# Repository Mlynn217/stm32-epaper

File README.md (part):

# stm32-epaper

An STM32-based e-reader using the Waveshare 6inch HD e-Paper HAT (IT8951 controller).

## Current Status

**Reads a real EPUB off an SD card and renders actual book pages on the physical panel.** On real
hardware, confirmed working end to end:
- STM32CubeMX → CMake → arm-none-eabi-gcc/Ninja → OpenOCD → ST-LINK build/flash/debug loop, from
  inside VSCode (tasks + launch configs for build, flash, debug, and a serial monitor)
- SPI1 communication with the IT8951 (panel resolution/FW/LUT version read back correctly, this
  panel's VCOM `-2.59V` set), the FMC/SDRAM (16MB, full read/write test passes), full-panel GC16
  grayscale refresh, and A2 (fast black/white-only partial refresh) mode
- **SD card storage** — SDIO+FatFS mount/read/write, a directory listing on every boot, and long
  filename support (`_USE_LFN=3`, heap-based — see TODO.md for why not `1`/`2`)
- **Fonts and page layout** — anti-aliased proportional bitmap fonts at reading-appropriate sizes
  (generated from a real TTF via `tools/gen_font.py`, not the tiny fixed-width fonts a low-res TFT
  would use), word-wrap, and pagination (a continuation-pointer API that can paginate arbitrarily
  long text one screen at a time without holding more than one page in memory)
- **An EPUB reader** (`Drivers/Epub/`, `Drivers/Inflate/`) — a minimal ZIP reader, a vendored
  reference DEFLATE decompressor, and tiny XML/HTML helpers, enough to parse `container.xml` → the
  OPF's manifest/spine → a chapter's XHTML → clean plain text, fed straight into the page-layout
  pipeline above. Validated against a real book (a purchased copy of *Mistborn: Secret History*) —
  see TODO.md for the debugging story, including a real FatFs/SDIO stale-read bug found and worked
  around along the way

Not done yet — see [TODO.md](TODO.md) for the full list, but the near-term highlights:
- No page-turn/chapter-navigation UI yet (currently auto-picks the first chapter with real text and
  shows up to 4 pages of it); no physical input handling
- Power management/battery life not started
- Custom PCB: the **v1 schematic is drafted in full** in `hardware/kicad/` (Power, MCU, Memory and
  Peripherals sheets). It's ERC-clean and machine-checked (pin mux, nets, footprint pads), but not
  yet reviewed by a person. v1 scope: the Waveshare HAT stays external on an SPI connector (see
  [Custom PCB (Planned)](#custom-pcb-planned))
- Custom PCB layout **nearly routed**: `hardware/kicad/stm32-epaper.kicad_pcb` is placed and
  routed (4 layers, enclosure-derived outline, inner planes) except **2 of ~460 connections**,
  both at the CAP1188. Some SDRAM/SDIO length and skew rules still need tuning (see TODO.md and
  [Layout rules](#layout-rules-main-board)). It's scripted end to end: placement,
  pre-routing, offline freerouting and our own last-mile router, with every attempt in
  `hardware/kicad/routing-log.md`. The side-wall electrode board (`hardware/electrode/`) is
  fully laid out and DRC-clean
- Enclosure: a **v0 parametric draft** in `hardware/enclosure/` (build123d). It passes its own fit
  checks and exports STEP/STL/3MF, but several dimensions are still placeholders and nothing has
  been printed (see [Enclosure](#enclosure-v0-draft))
- No license chosen yet

## Overview

Goal: a standalone, **handheld, Kindle-style** e-reader built around Waveshare's
[6inch HD e-Paper HAT](https://www.waveshare.com/6inch-hd-e-paper-hat.htm) (1448×1072, 16-level
grayscale, IT8951 controller), driven by an STM32 host. The Discovery board is a bring-up platform;
the end goal is a custom PCB — see [Custom PCB (Planned)](#custom-pcb-planned) below for the current
draft of hardware decisions for that board.

**Phase 1 host: STM32F469I-DISCO.** It has its own onboard RGB LCD, but that's not why it was
picked — it's the FMC-attached SDRAM that matters. The IT8951 needs a host-side frame buffer too
large for any STM32's internal SRAM, which is exactly why Waveshare's own reference design pairs
the IT8951 with an STM32F429 board (Open429I) that has external SDRAM bolted on. The F469-Disco
already has SDRAM on the FMC bus (normally used for its own LCD), so we get that requirement for
free. It's a bring-up/development platform for proving out the driver and architecture — the final
product host may end up being a smaller, lower-power part once the design is proven.

## Hardware

### Display: Waveshare 6inch HD e-Paper HAT

- Panel: 6", 1448×1072, black/white, 16 grayscale levels (1–4 bpp)
- Controller: IT8951 (on the HAT/driver board)
- Full refresh: <1s. Refresh power ~0.6W typ, standby ~0.3W typ
- Host interface options: SPI / I80 (parallel) / I2C / USB (USB requires an NDA with Waveshare —
  not an option for us)
- **Using SPI** — Waveshare's own recommendation ("fewer pins, easy to use"). I80 is faster but
  needs 16 data pins plus control lines, which would compete with the Discovery board's other
  onboard peripherals; I2C is too slow for meaningful refresh rates.
- Operating voltage: 5V
- Outline: 138.4×101.8×0.67mm; active display area: 122.356×90.584mm
- Viewing angle: >170°; operating temp 0–50°C, storage -25–70°C
- Each physical panel has a unique **VCOM** value printed on its FPC cable that must be set in
  firmware for correct grayscale/contrast. **This panel's VCOM is `-2.59V`** → pass `2590` (mV
  magnitude) to `EPD_IT8951_Init()`/`EPD_IT8951_SetVCOM()`.

### Host: STM32F469I-DISCO

- STM32F469NIH6 — Cortex-M4F, 2MB flash, 384KB internal SRAM
- FMC-attached SDRAM onboard (normally the framebuffer for the board's own RGB LCD) — repurposed
  here as the IT8951 frame buffer
- Onboard ST-LINK/V2-1 — no external debug probe needed

### Wiring

Final pin assignment for the F469-Disco, chosen by checking every candidate pin against the MCU's
full alternate-function list and cross-referencing everything already enabled in the `.ioc` (FMC,
DSIHOST/LTDC, I2C1/2, SAI1, SDIO, QUADSPI, USART3/6, USB_OTG_FS, TIM1) — no conflicts:

| IT8951 HAT pin | Signal              | STM32 pin | Discovery connector      | Pin # | Silkscreen label | Wire color |
|----------------|---------------------|-----------|--------------------------|-------|-------------------|------------|
| 5V             | Power               | —         | CN6 (Arduino Power)      | 5     | `+5V`             | Grey       |
| GND            | Ground              | —         | CN6 (Arduino Power)      | 6/7   | `GND`             | Black      |
| SCK            | SPI1_SCK            | PA5       | CN12 (Extension header)  | 7     | —                 | Orange     |
| MISO           | SPI1_MISO           | PB4       | CN12 (Extension header)  | 5     | —                 | Blue       |
| MOSI           | SPI1_MOSI           | PB5       | CN12 (Extension header)  | 9     | —                 | Yellow     |
| CS             | GPIO_Output, PP, idle high | PA4 | CN8 (Arduino Analog)   | 6     | `A5`              | Green      |
| RST            | GPIO_Output, PP, idle high | PB1 | CN8 (Arduino Analog)   | 1     | `A0`              | White      |
| HRDY (busy)    | GPIO_Input          | PA2       | CN7 (Arduino Digital)    | 6     | `D5`              | Purple     |

Notes:
- SPI1's SCK/MISO/MOSI are only broken out on **CN12**, the 16-pin 2.54mm extension header on the
  underside of the board — not on the Arduino headers. CS/RST/HRDY are split across CN8 and CN7
  instead, so wiring the HAT means jumpers from three different connectors plus CN6, not one.
- CN8 pin 6 (`A5`) defaults to PA4 via solder bridges SB10/SB12 (closed by default) — worth a
  continuity check with a multimeter before trusting it, since those can be reconfigured.
- CS/RST are push-pull, idle **high** (both signals are active-low on the IT8951 side — CS is only
  pulled low during a transaction, RST is only pulsed low as a deliberate reset, driven by the
  driver's init code rather than left low by default).
- SPI1 clock: **11.25 MHz** (APB2/8 off a 90MHz APB2 clock). The IT8951's datasheet (Table 9-4, SPI
  AC Characteristics) caps `fSCLK` at 24MHz; 11.25MHz leaves comfortable margin for jumper-wire
  wiring rather than a tightly-routed PCB. `hspi1.Init.BaudRatePrescaler` in `Core/Src/main.c` and
  `SPI1.CalculateBaudRate` in the `.ioc` are both set to match.
- HRDY (busy) is active-low (low = busy). All three IT8951-side GPIOs are currently `GPIO_NOPULL`
  (no pull-up/down) — a defensive pull-up was considered for the brief post-reset window before
  `MX_GPIO_Init()` runs, but wasn't applied; not required since these are actively driven once init
  runs, just an optional safety margin if boot-order issues ever show up.

## Custom PCB (Planned)

In progress. The KiCad project is in `hardware/kicad/`, and the **v1 schematic is drafted in full**:
Power, MCU, Memory and Peripherals sheets. PCB layout is next (see TODO.md). These are the
**current draft hardware decisions**, recorded here so context isn't lost between sessions. They're still open to change
while the schematic takes shape. The Discovery board plus the Waveshare HAT above stays the bring-up
platform until the PCB is built.

**Board scope (decided 2026-09-22):**
- **v1 PCB:** power, MCU, memory, navigation/input and the other peripherals. The **Waveshare
  IT8951 HAT stays an external module**, connected over an SPI connector, with the board supplying
  its 5 V.
- **Deferred to a later revision:** a bare IT8951 IC with its own panel PMIC (see
  [Display](#display) for what that involves).

### Input System

| Control | Component | Interface | Notes |
|---|---|---|---|
| Prev / Next page | CAP1188-1-SL (Microchip) | I²C + ALERT interrupt | 8-channel; side-wall electrodes |
| Side-wall electrodes | 2 small electrode boards (0.8 mm FR4), 2 pads each | JST-SH cable per side (J302/J303) | Pads pressed against the inside of each side wall; plastic wall as dielectric (up to ~4mm) |
| Library / menu scroll | Bourns PEC11R-4220F-S0024 | 2× GPIO (A, B quadrature) | 24 detents / 24 pulses per revolution, 20mm flatted shaft (the M7 bushing leaves too little of a 15mm shaft for the knob to grip through the front face; the Discovery bring-up used the 15mm -4215F) |
| Confirm / select | Encoder push | 1× GPIO (SW) | Built into the PEC11R (the "S" in S0024) |
| Power / wake | Alps SKRTLAE010 side-actuated tact switch | 1× GPIO (WKUP pin) | Bottom edge, on the main PCB, pressed through a flexure tab in the wall; physical, not capacitive |

Layout: cap-touch zones on left/right side walls (thumb rest). The encoder knob is on the front
face below the display (the PEC11R is vertical-mount), and the power button is on the bottom edge
next to microSD and USB-C (decided 2026-09-23, see [Enclosure](#enclosure-v0-draft)).

**Considered and set aside (open to revisiting if requirements change):**
- PSP-style analog joystick (COM-09426): analog noise, no click function, and its resistive divider
  draws current continuously, which is wrong for a device that mostly sleeps.
- On-glass bezel capacitive (ITO film): manufacturing complexity; side-wall electrode boards achieve
  the same result more simply.
- Copper tape or a flex strip for the side-wall electrodes: either works, but small rigid boards
  give repeatable pad geometry, can carry ESD parts, and cost pennies in the same PCB order (flex
  is ~10× the price for no benefit here).

### MCU, Memory & Storage

| Component | Part | Interface | Role |
|---|---|---|---|
| MCU | STM32F469IIT6 (LQFP176) | — | Same die as the Disco's F469NI, but a hand-/JLC-assemblable package instead of TFBGA216. Confirm the pin budget (FMC SDRAM + SDIO + QSPI + SPI + I²C + USB) in CubeMX before layout |
| SDRAM | IS42S16400J-6TLI | FMC 16-bit | **64 Mbit = 8 MB** (earlier notes wrongly said 16 MB; that's the Disco's chip). Plenty: ~776 KB frame buffer + the 4 MB text/EPUB buffer. Keep it, because the whole-file-in-RAM FatFs/SDIO workaround depends on it |
| QSPI NOR Flash | W25Q128JV (16 MB) | QSPI | Firmware + fonts. (N25Q128A dropped: Micron's legacy line, superseded by MT25Q) |
| microSD slot | TBD (Molex 1040310811 or GCT MSD-4-A candidates) | SDIO 4-bit | Book library (user-swappable) |

SDRAM is volatile. It does **not** replace storage; book files live on microSD.

### Display

**v1:** the Waveshare 6" HD HAT, off-board on an SPI connector. The HAT takes 5 V (from the
TPS61023 boost) and has 3.3 V SPI logic.

**Later revision: a bare IT8951 IC.** The IT8951 datasheet (`docs/IT8951_D_V0.2.4.3_20170728.pdf`)
shows this is **not** a "just run everything from 3.3 V" change (an earlier note here claimed it
was). It needs:
- **A 1.8 V core supply** (VCCK, VCC18A and VCC_SDR, each 1.8 V ±0.09 V) as well as 3.3 V for I/O and
  analog.
- **A power-up order: 1.8 V stable first, then 3.3 V, then reset released.** A 1.8 V LDO fed
  *from* 3.3 V can't meet that. One fix: feed the LDO from VSYS and switch the IT8951's 3.3 V on
  afterwards with a load switch.
- **A 12 MHz crystal, and its own SPI NOR flash** holding the panel's **waveform file**. The
  waveform is panel-specific and comes from the panel maker; the HAT ships with it in its flash.
  **Getting it is the biggest risk of going bare-IC.**
- **A TPS65185/TPS65186 panel PMIC** with its own inductors, diodes and caps (for VCOM and the
  panel's high voltages), plus the panel FPC connector.
- The IT8951 has **built-in** SDRAM (32 Mb, or 64 Mb on the -64 variants), so it needs no external
  DRAM. It's rated 0–70 °C.

### Power Architecture

**Cell chemistry: 1-cell LiPo pouch (3.7 V nominal, 4.2 V full), with a protection board.**
Switched from LiFePO4 on 2026-09-23. Small, flat LFP pouches turned out to be practically
unobtainable in the US: sample requests to overseas cell makers only. Protected LiPo pouches with
JST-PH 2.0 leads are stocked everywhere (Adafruit, SparkFun, DigiKey). What each chemistry offers:

| | LiFePO4 (previous choice) | LiPo (now) |
|---|---|---|
| Thermal runaway onset | ~270 °C | ~150 °C |
| Cycle life | 2000–3000 | ~300–500 |
| Energy density | lower | ~2× |
| Flat pouches in the US | poor | excellent |
| Discharge curve | flat (voltage says little about charge) | sloped (voltage is a usable fuel estimate) |

The safety gap is handled the way phones and e-readers handle it:
- A protected cell.
- A charger that watches cell temperature through an NTC and refuses to charge outside ~0–50 °C.
- An undervoltage cutoff.
- A sensible enclosure: leave room for the pouch to swell.

~300–500 cycles is still years of use for a reader charged every few weeks.

**Candidate cells (ordered 2026-09-23):** two EEMB protected LiPo packs with JST-PH 2.0 leads.
They share a 34.5 mm × ~52 mm outline and differ only in thickness. Figures come from EEMB's
specs: the [LP963450-PCM-LD pack spec](https://m.media-amazon.com/images/I/81dlwMxaX9L.pdf) (doc
ZJQM-RD-SPC-H1817) and the [LP603449 cell spec](https://www.eemb.com/product-147) (ZJQM-RD-SPC-H0482;
no pack-level sheet found).

| | EEMB LP603449 (pack) | EEMB LP963450-PCM-LD |
|---|---|---|
| Capacity | 1100 mAh (1000 min) | 1800 mAh (1700 min) |
| Pack envelope (max) | 6.3 × 34.5 × ~52 mm (cell body 50 mm; +PCM assumed as on the 963450) | **9.9 × 34.5 × 52 mm** |
| Weight | ~22 g | ~36 g |
| Charge | 4.20 V CC/CV, max 1C (1100 mA) | 4.2 V CC/CV, max 1C (1800 mA) |
| **Cold charging** | assumed as 963450 | **0–20 °C: ≤ 0.3C** |
| Charge temperature | 0–45 °C | 0–45 °C |
| Discharge | max 2C, cell cutoff 2.75 V | max 2C (3.6 A); pack limit 1 A continuous, 2 A for 3 s |
| Protection board (963450 spec) | assumed same family | overcharge 4.28 ± 0.05 V; **over-discharge 3.0 ± 0.1 V** (releases at 3.5 V) |
| Leads | JST-PH 2.0 | red (+) / black (−) UL1007 AWG26, **50 ± 3 mm**, JST PHR-02, from the PCM edge |
| Cycle life | ≥ 500 at 0.5C, ≥ 800 at 0.2C | ≥ 800 (min) |

**How the design fits them:**
- **Charge current:** ~296 mA (265–324 mA worst case), ≤ 0.3C of the smaller cell, so both cells are
  within spec at any charge temperature.
- **Charge timer:** 7.2–12 h, long enough for the 1800 mAh cell.
- **Cutoff order:** hardware cutoff at ~3.20 V, above the protection board's 3.0 V (firmware shuts
  down at ~3.4 V first).
- **Current:** peak draw ~0.7 A, under the pack's 1 A continuous limit.
- **Hot end:** the cells' 45 °C charging limit is handled in firmware (see the Power sheet section).

**Battery bay (enclosure input).** Size the bay for the 963450: **52 × 34.5 × 9.9 mm max, plus
~0.5 mm on each face for swelling**. Use a ~3.6 mm spacer when fitting the LP603449. Other points:
- The PCM strip and the lead exit are on one 34.5 mm edge. The 50 mm lead needs a route to J2 (keep
  J2 within ~40 mm of that edge, or allow slack).
- Keep the pouch clear of sharp edges and screw bosses.
- RT1 (the charger's NTC) is a leaded Murata NXFT15XH103 soldered to pads on the PCB, with its head
  taped to the pouch (the cell sits beside the PCB, not over it).
- **Polarity isn't shown by pin in EEMB's drawings** (only red = +). Check J2 pin 1 = + with a meter
  before plugging a cell in.

**Power tree, v1 (external Waveshare HAT):**
```
USB-C VBUS ──► BQ24073 charger + power path ──► VSYS (4.4V regulated with USB; = cell on battery)
                      └──► LiPo cell (3.0–4.2V)          4.2V CV, NTC-qualified, ~500mA
VSYS ──► TPS63802 buck-boost → 3.3V                        STM32, SDRAM, QSPI, microSD, CAP1188, encoder, buttons
           └── EN = VSYS divider: OFF < ~3.20V, ON > ~3.52V (undervoltage cutoff)
VSYS ──► TPS61023 boost → 5V                               external Waveshare HAT (MCU-enabled)
cell ──► MCP1700 3.0V LDO → MCU VBAT                       RTC backup
cell ──► 1M/1M divider → PA3 (ADC)                         firmware battery measurement
```

**Battery protection (undervoltage).** The charger only charges; it does **nothing** to stop
over-discharge. Protection is layered:
1. **Firmware (primary).** Measure the cell on `VBAT_SENSE` (PA3, 1M/1M divider, ~2 µA). At about
   3.4 V under light load, shut down gracefully: save state, leave a "please charge" screen on the
   e-ink (it holds with no power), then enter standby. LiPo's sloped curve makes this voltage a
   reasonable fuel estimate too.
2. **Hardware backstop.** The TPS63802's EN pin has a precise threshold (1.10 V rising / 1.00 V
   falling). A 2.2 MΩ/1.0 MΩ divider from VSYS turns the 3.3 V rail off below ~3.20 V and back on
   above ~3.52 V (±3%), costing ~1.1 µA. This catches a hung firmware or a drain during sleep.
3. **Cell protection board (required).** Buy only protected cells. The protection board is the
   only thing that truly disconnects the cell (typically ~2.5–3.0 V), and it also handles shorts
   and overcurrent.

**Sleep current:** the regulator's own draw is now ~11 µA (TPS63802), down from ~50 µA for the
TPS63070 it replaced. Total design floor ≈ 11 µA (TPS63802) + ~1.1 µA (cutoff divider) + ~2 µA
(battery sense divider) + ~1.6 µA (RTC LDO) + ~2.4 µA (MCU standby) + CAP1188 (5 µA deep sleep,
~50 µA if it watches for a touch). That's with the peripheral rail switched off; keeping the SDRAM
in self-refresh instead adds ~2 mA max.

**Peripheral load switch: fitted on v1** (decided 2026-09-23).
- **What it does:** a TPS22965 gates `3V3_PERIPH` (SDRAM, QSPI flash, microSD). Without it those
  parts stay powered in STANDBY, a ~2–20 mA idle floor (~70 mAh/day). With it, idle is ~0.5–2 mAh/day,
  which means months on the shelf.
- **Firmware policy:** STOP with SDRAM self-refresh between page turns; STANDBY with the peripheral
  rail off after a few minutes idle, reloading the book from SD on wake.

**Still reserved for v2** (target < 10 µA): a **TPS63900** nanopower buck-boost (75 nA quiescent)
as an always-on `3V3_AON` rail for the MCU and CAP1188. It replaced the earlier MAX17222 idea: that
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
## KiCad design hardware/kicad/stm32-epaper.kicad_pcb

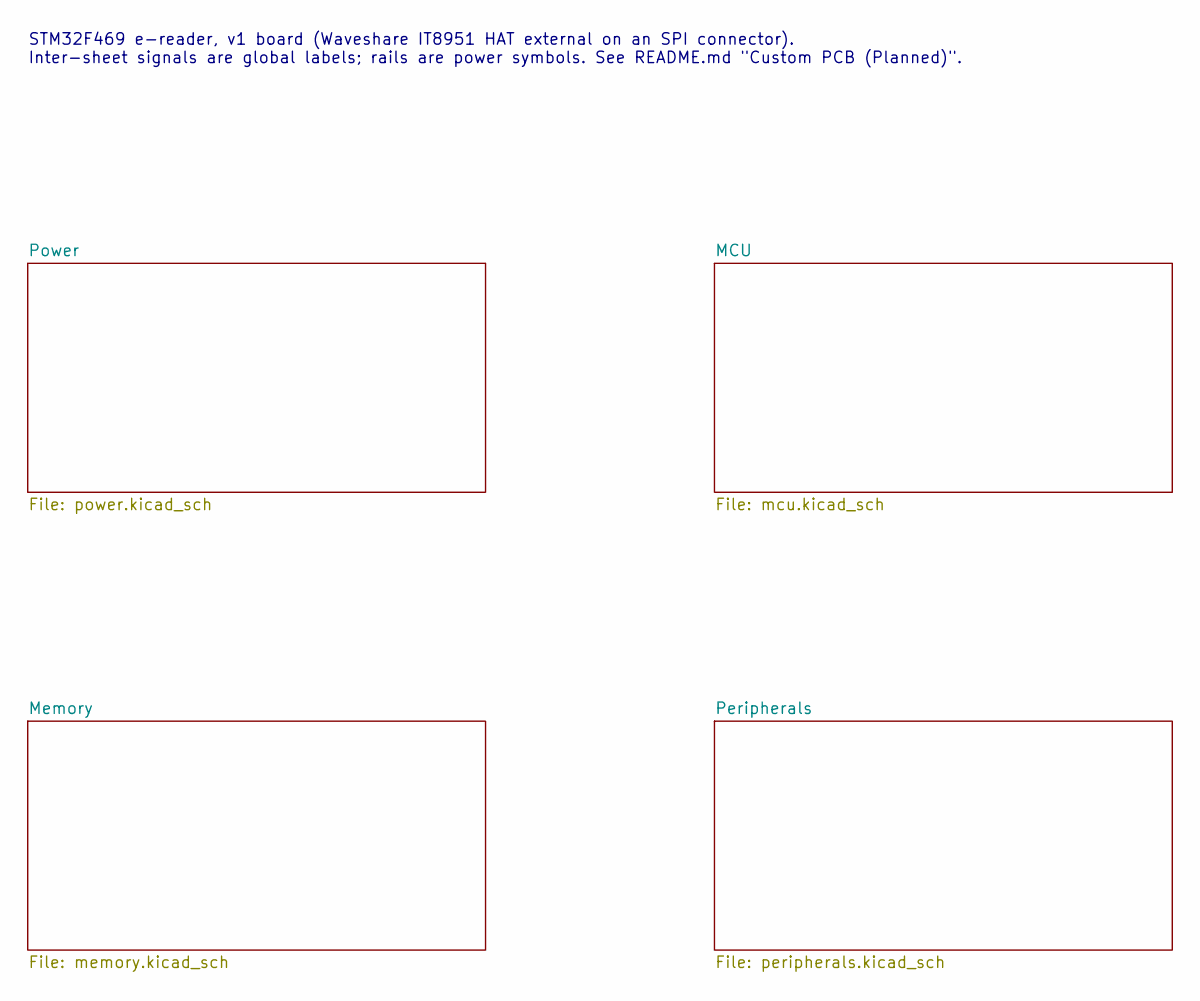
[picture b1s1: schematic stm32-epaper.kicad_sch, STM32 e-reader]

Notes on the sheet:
STM32F469 e-reader, v1 board (Waveshare IT8951 HAT external on an SPI connector). Inter-sheet signals are global labels; rails are power symbols. See README.md "Custom PCB (Planned)".

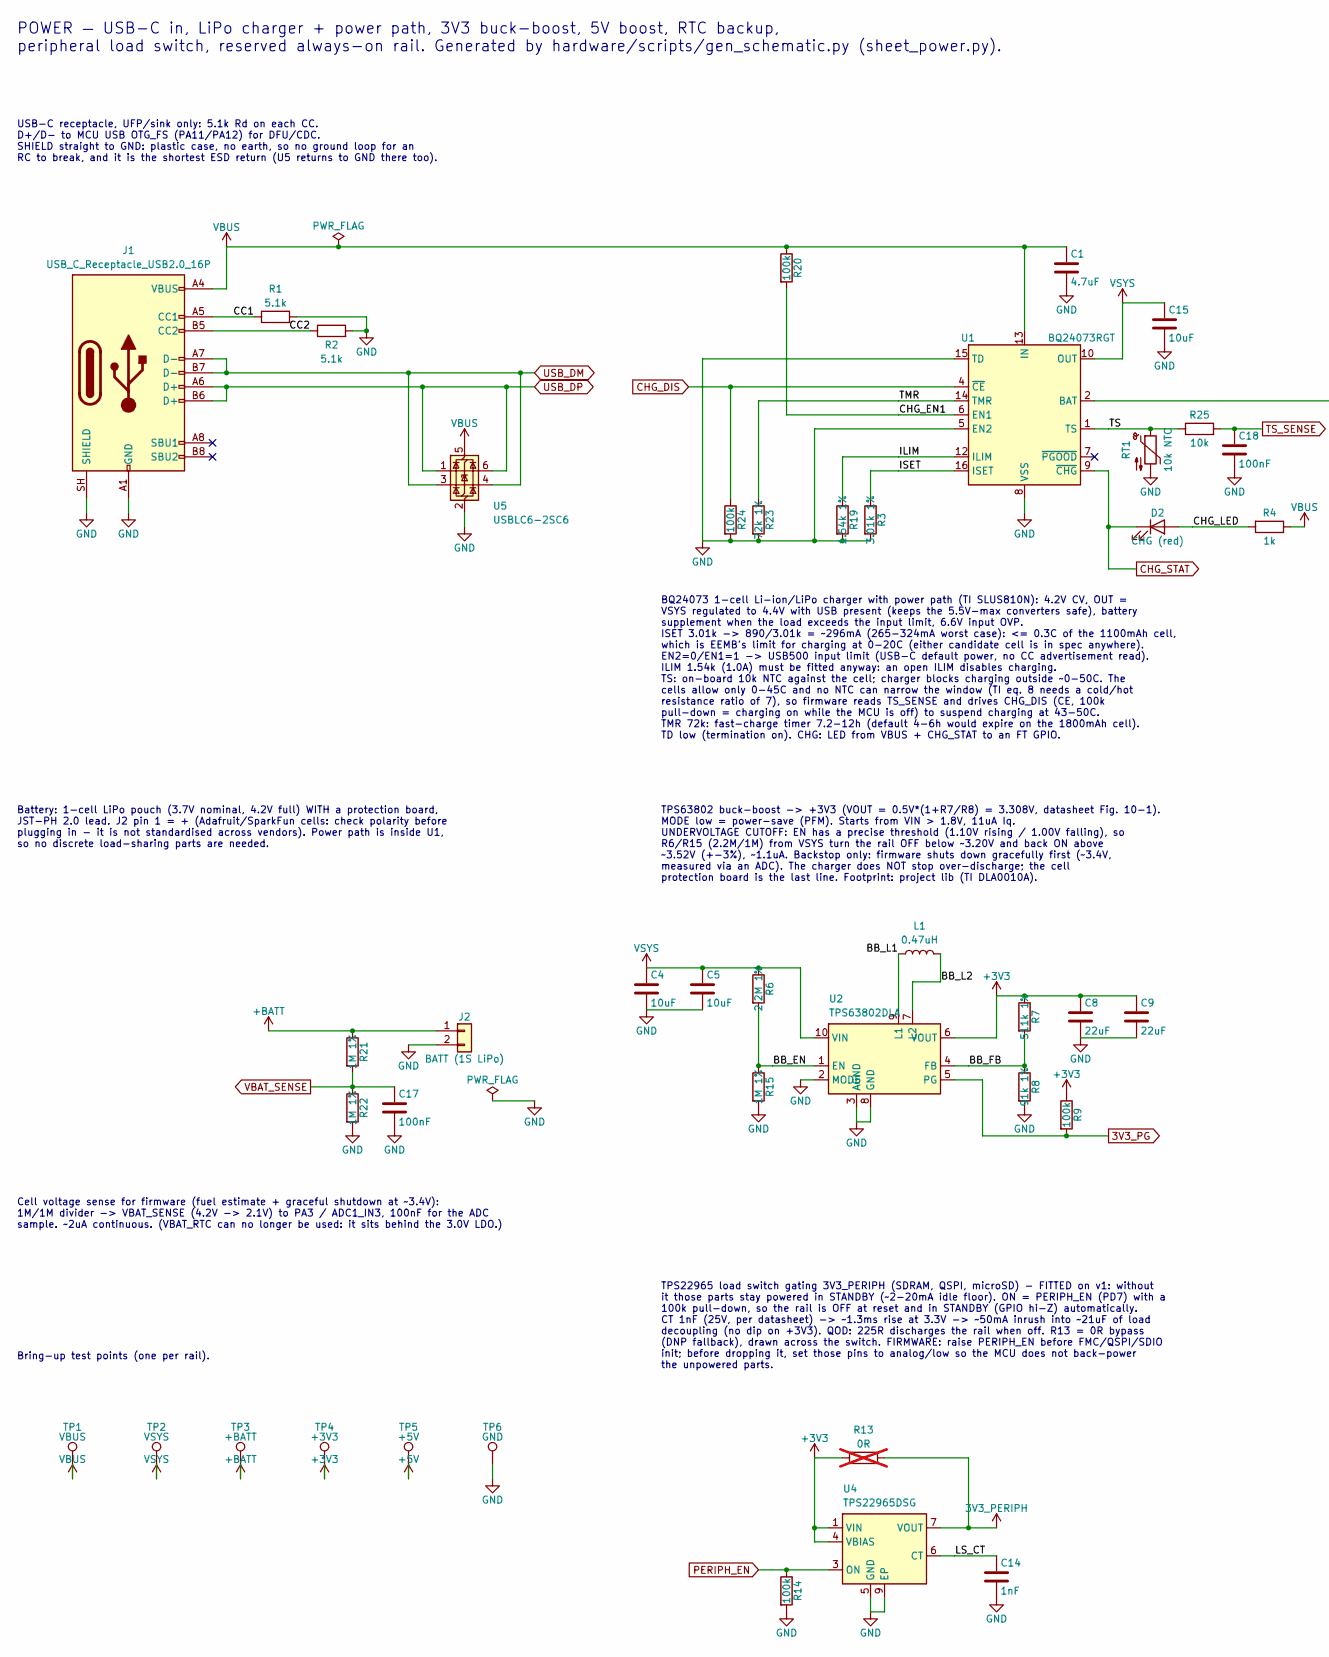
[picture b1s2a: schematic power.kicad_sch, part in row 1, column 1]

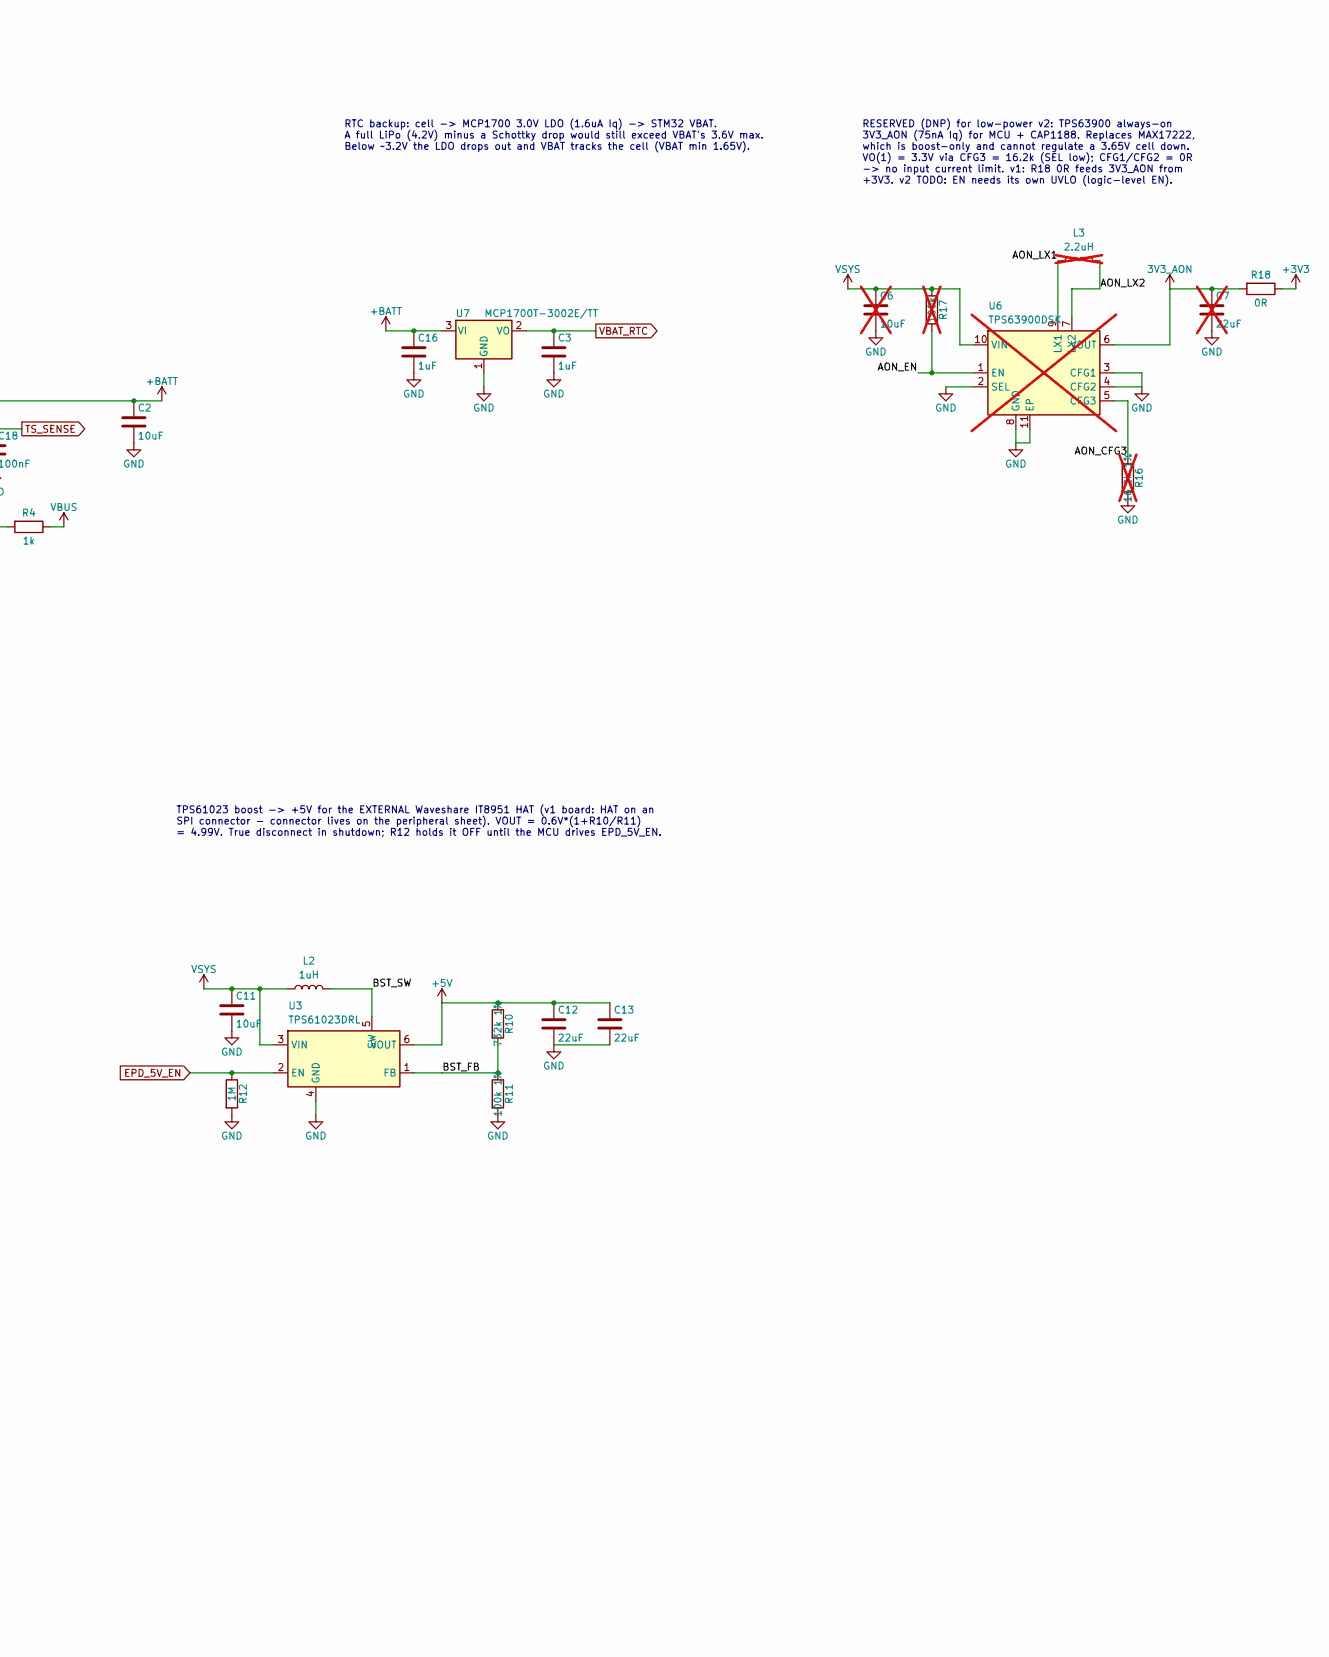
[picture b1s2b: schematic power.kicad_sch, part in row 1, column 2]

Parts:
C1: 4.7uF; C_0603_1608Metric; Voltage 10V
C2, C4, C5, C15: 10uF; C_0603_1608Metric; Voltage 10V
C3, C16: 1uF; C_0402_1005Metric
C6: 10uF; C_0603_1608Metric; not fitted
C7: 22uF; C_0603_1608Metric; not fitted
C8, C9: 22uF; C_0603_1608Metric
C11: 10uF; C_0603_1608Metric
C12, C13: 22uF; C_0805_2012Metric
C14: 1nF; C_0402_1005Metric; Voltage 25V X7R (CT pin can reach 12V)
C17, C18: 100nF; C_0402_1005Metric
D2: CHG (red); LED_0603_1608Metric
J1: USB_C_Receptacle_USB2.0_16P; USB_C_Receptacle_GCT_USB4105-xx-A_16P_TopMnt_Horizontal; MPN GCT USB4105-GF-A
J2: BATT (1S LiPo); JST_PH_S2B-PH-SM4-TB_1x02-1MP_P2.00mm_Horizontal
L1: 0.47uH; L_Murata_DFE201610P; MPN DFE201612E-R47M=P2 (Isat 5.5A, 26mR; Mu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
L2: 1uH; L_Murata_DFE201610P; MPN DFE201612E-1R0M=P2 (Isat 4.0A >= TPS610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
L3: 2.2uH; L_Murata_DFE201610P; MPN DFE201612E-2R2M=P2 (TPS63900 datasheet 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; not fitted
R1, R2: 5.1k; R_0402_1005Metric
R3: 3.01k 1%; R_0402_1005Metric
R4: 1k; R_0402_1005Metric
R6: 2.2M 1%; R_0402_1005Metric
R7: 511k 1%; R_0402_1005Metric
R8: 91k 1%; R_0402_1005Metric
R9, R14, R20, R24: 100k; R_0402_1005Metric
R10: 732k 1%; R_0402_1005Metric
R11: 100k 1%; R_0402_1005Metric
R12: 1M; R_0402_1005Metric
R13: 0R; R_0603_1608Metric; not fitted
R15, R21, R22: 1M 1%; R_0402_1005Metric
R16: 16.2k 1%; R_0402_1005Metric; not fitted
R17: 100k; R_0402_1005Metric; not fitted
R18: 0R; R_0603_1608Metric
R19: 1.54k 1%; R_0402_1005Metric
R23: 72k 1%; R_0402_1005Metric
R25: 10k; R_0402_1005Metric
RT1: 10k NTC; SolderWire-0.1sqmm_1x02_P3.6mm_D0.4mm_OD1mm; MPN NXFT15XH103FA2B (Murata leaded film NTC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
TP1: VBUS; TestPoint_Pad_D1.5mm
TP2: VSYS; TestPoint_Pad_D1.5mm
TP3: +BATT; TestPoint_Pad_D1.5mm
TP4: +3V3; TestPoint_Pad_D1.5mm
TP5: +5V; TestPoint_Pad_D1.5mm
TP6: GND; TestPoint_Pad_D1.5mm
U1: BQ24073RGT; VQFN-16-1EP_3x3mm_P0.5mm_EP1.6x1.6mm; MPN BQ24073RGTR
U2: TPS63802DLA; Texas_DLA0010A_VSON-HR-10_2x3mm_P0.5mm; MPN TPS63802DLAR
U3: TPS61023DRL; SOT-563; MPN TPS61023DRLR
U4: TPS22965DSG; Texas_DSG0008A_WSON-8-1EP_2x2mm_P0.5mm_EP0.9x1.6mm; MPN TPS22965DSGR
U5: USBLC6-2SC6; SOT-23-6
U6: TPS63900DSK; WSON-10-1EP_2.5x2.5mm_P0.5mm_EP1.2x2mm; MPN TPS63900DSKR; not fitted
U7: MCP1700T-3002E/TT; SOT-23; MPN MCP1700T-3002E/TT

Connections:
3V3_AON: C7.1, R18.2, U6.6 (VOUT); also elsewhere on the board
3V3_PERIPH: R13.2, U4.7 (VOUT), U4.8 (VOUT); also elsewhere on the board
3V3_PG: R9.2, U2.5 (PG); also elsewhere on the board
+3V3: C8.1, C9.1, R7.1, R9.1, R13.1, R18.1, TP4.1, U2.6 (VOUT), U4.1 (VIN), U4.2 (VIN), U4.4 (VBIAS)
+5V: C12.1, C13.1, R10.1, TP5.1, U3.6 (VOUT); also elsewhere on the board
+BATT: C2.1, C16.1, J2.1, R21.1, TP3.1, U1.2 (BAT), U1.3 (BAT), U7.3 (VI)
/Power/AON_CFG3: R16.1, U6.5 (CFG3)
/Power/AON_EN: R17.2, U6.1 (EN)
/Power/AON_LX1: L3.1, U6.9 (LX1)
/Power/AON_LX2: L3.2, U6.7 (LX2)
/Power/BB_EN: R6.2, R15.1, U2.1 (EN)
/Power/BB_FB: R7.2, R8.1, U2.4 (FB)
/Power/BB_L1: L1.1, U2.9 (L1)
/Power/BB_L2: L1.2, U2.7 (L2)
/Power/BST_FB: R10.2, R11.1, U3.1 (FB)
/Power/BST_SW: L2.2, U3.5 (SW)
/Power/CC1: J1.A5 (CC1), R1.1
/Power/CC2: J1.B5 (CC2), R2.1
/Power/CHG_EN1: R20.2, U1.6 (EN1)
/Power/CHG_LED: D2.2 (A), R4.2
/Power/ILIM: R19.1, U1.12 (ILIM)
/Power/ISET: R3.1, U1.16 (ISET)
/Power/LS_CT: C14.1, U4.6 (CT)
/Power/TMR: R23.1, U1.14 (TMR)
/Power/TS: R25.1, RT1.1, U1.1 (TS)
CHG_DIS: R24.1, U1.4 (~CE); also elsewhere on the board
CHG_STAT: D2.1 (K), U1.9 (~CHG); also elsewhere on the board
EPD_5V_EN: R12.1, U3.2 (EN); also elsewhere on the board
GND: C1.2, C2.2, C3.2, C4.2, C5.2, C6.2, C7.2, C8.2, C9.2, C11.2, C12.2, C13.2, C14.2, C15.2, C16.2, C17.2, C18.2, J1.A1 (GND), J1.A12 (GND), J1.B1 (GND), J1.B12 (GND), J1.SH (SHIELD), J2.2, R1.2, R2.2, R3.2, R8.2, R11.2, R12.2, R14.2, R15.2, R16.2, R19.2, R22.2, R23.2, R24.2, RT1.2, TP6.1, U1.5 (EN2), U1.8 (VSS), U1.15 (TD), U1.17 (VSS), U2.2 (MODE), U2.3 (AGND), U2.8 (GND), U3.4 (GND), U4.5 (GND), U4.9 (EP), U5.2 (GND), U6.2 (SEL), U6.3 (CFG1), U6.4 (CFG2), U6.8 (GND), U6.11 (EP), U7.1 (GND); also elsewhere on the board
PERIPH_EN: R14.1, U4.3 (ON); also elsewhere on the board
TS_SENSE: C18.1, R25.2; also elsewhere on the board
USB_DM: J1.A7 (D-), J1.B7 (D-), U5.3 (I/O2), U5.4 (I/O2); also elsewhere on the board
USB_DP: J1.A6 (D+), J1.B6 (D+), U5.1 (I/O1), U5.6 (I/O1); also elsewhere on the board
VBAT_RTC: C3.1, U7.2 (VO); also elsewhere on the board
VBAT_SENSE: C17.1, R21.2, R22.1; also elsewhere on the board
VBUS: C1.1, J1.A4 (VBUS), J1.A9 (VBUS), J1.B4 (VBUS), J1.B9 (VBUS), R4.1, R20.1, TP1.1, U1.13 (IN), U5.5 (VBUS); also elsewhere on the board
VSYS: C4.1, C5.1, C6.1, C11.1, C15.1, L2.1, R6.1, R17.1, TP2.1, U1.10 (OUT), U1.11 (OUT), U2.10 (VIN), U3.3 (VIN), U6.10 (VIN)

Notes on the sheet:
POWER — USB-C in, LiPo charger + power path, 3V3 buck-boost, 5V boost, RTC backup, peripheral load switch, reserved always-on rail. Generated by hardware/scripts/gen_schematic.py (sheet_power.py).
USB-C receptacle, UFP/sink only: 5.1k Rd on each CC. D+/D- to MCU USB OTG_FS (PA11/PA12) for DFU/CDC. SHIELD straight to GND: plastic case, no earth, so no ground loop for an RC to break, and it is the shortest ESD return (U5 returns to GND there too).
BQ24073 1-cell Li-ion/LiPo charger with power path (TI SLUS810N): 4.2V CV, OUT = VSYS regulated to 4.4V with USB present (keeps the 5.5V-max converters safe), battery supplement when the load exceeds the input limit, 6.6V input OVP. ISET 3.01k -> 890/3.01k = ~296mA (265-324mA worst case): <= 0.3C o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
RTC backup: cell -> MCP1700 3.0V LDO (1.6uA Iq) -> STM32 VBAT. A full LiPo (4.2V) minus a Schottky drop would still exceed VBAT's 3.6V max. Below ~3.2V the LDO drops out and VBAT tracks the cell (VBAT min 1.65V).
RESERVED (DNP) for low-power v2: TPS63900 always-on 3V3_AON (75nA Iq) for MCU + CAP1188. Replaces MAX17222, which is boost-only and cannot regulate a 3.65V cell down. VO(1) = 3.3V via CFG3 = 16.2k (SEL low); CFG1/CFG2 = 0R -> no input current limit. v1: R18 0R feeds 3V3_AON from +3V3. v2 TODO: EN n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
Battery: 1-cell LiPo pouch (3.7V nominal, 4.2V full) WITH a protection board, JST-PH 2.0 lead. J2 pin 1 = + (Adafruit/SparkFun cells: check polarity before plugging in - it is not standardised across vendors). Power path is inside U1, so no discrete load-sharing parts are needed.
Cell voltage sense for firmware (fuel estimate + graceful shutdown at ~3.4V): 1M/1M divider -> VBAT_SENSE (4.2V -> 2.1V) to PA3 / ADC1_IN3, 100nF for the ADC sample. ~2uA continuous. (VBAT_RTC can no longer be used: it sits behind the 3.0V LDO.)
TPS63802 buck-boost -> +3V3 (VOUT = 0.5V*(1+R7/R8) = 3.308V, datasheet Fig. 10-1). MODE low = power-save (PFM). Starts from VIN > 1.8V, 11uA Iq. UNDERVOLTAGE CUTOFF: EN has a precise threshold (1.10V rising / 1.00V falling), so R6/R15 (2.2M/1M) from VSYS turn the rail OFF below ~3.20V and back ON a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
TPS61023 boost -> +5V for the EXTERNAL Waveshare IT8951 HAT (v1 board: HAT on an SPI connector - connector lives on the peripheral sheet). VOUT = 0.6V*(1+R10/R11) = 4.99V. True disconnect in shutdown; R12 holds it OFF until the MCU drives EPD_5V_EN.
TPS22965 load switch gating 3V3_PERIPH (SDRAM, QSPI, microSD) - FITTED on v1: without it those parts stay powered in STANDBY (~2-20mA idle floor). ON = PERIPH_EN (PD7) with a 100k pull-down, so the rail is OFF at reset and in STANDBY (GPIO hi-Z) automatically. CT 1nF (25V, per datasheet) -> ~1.3ms 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
Bring-up test points (one per rail).

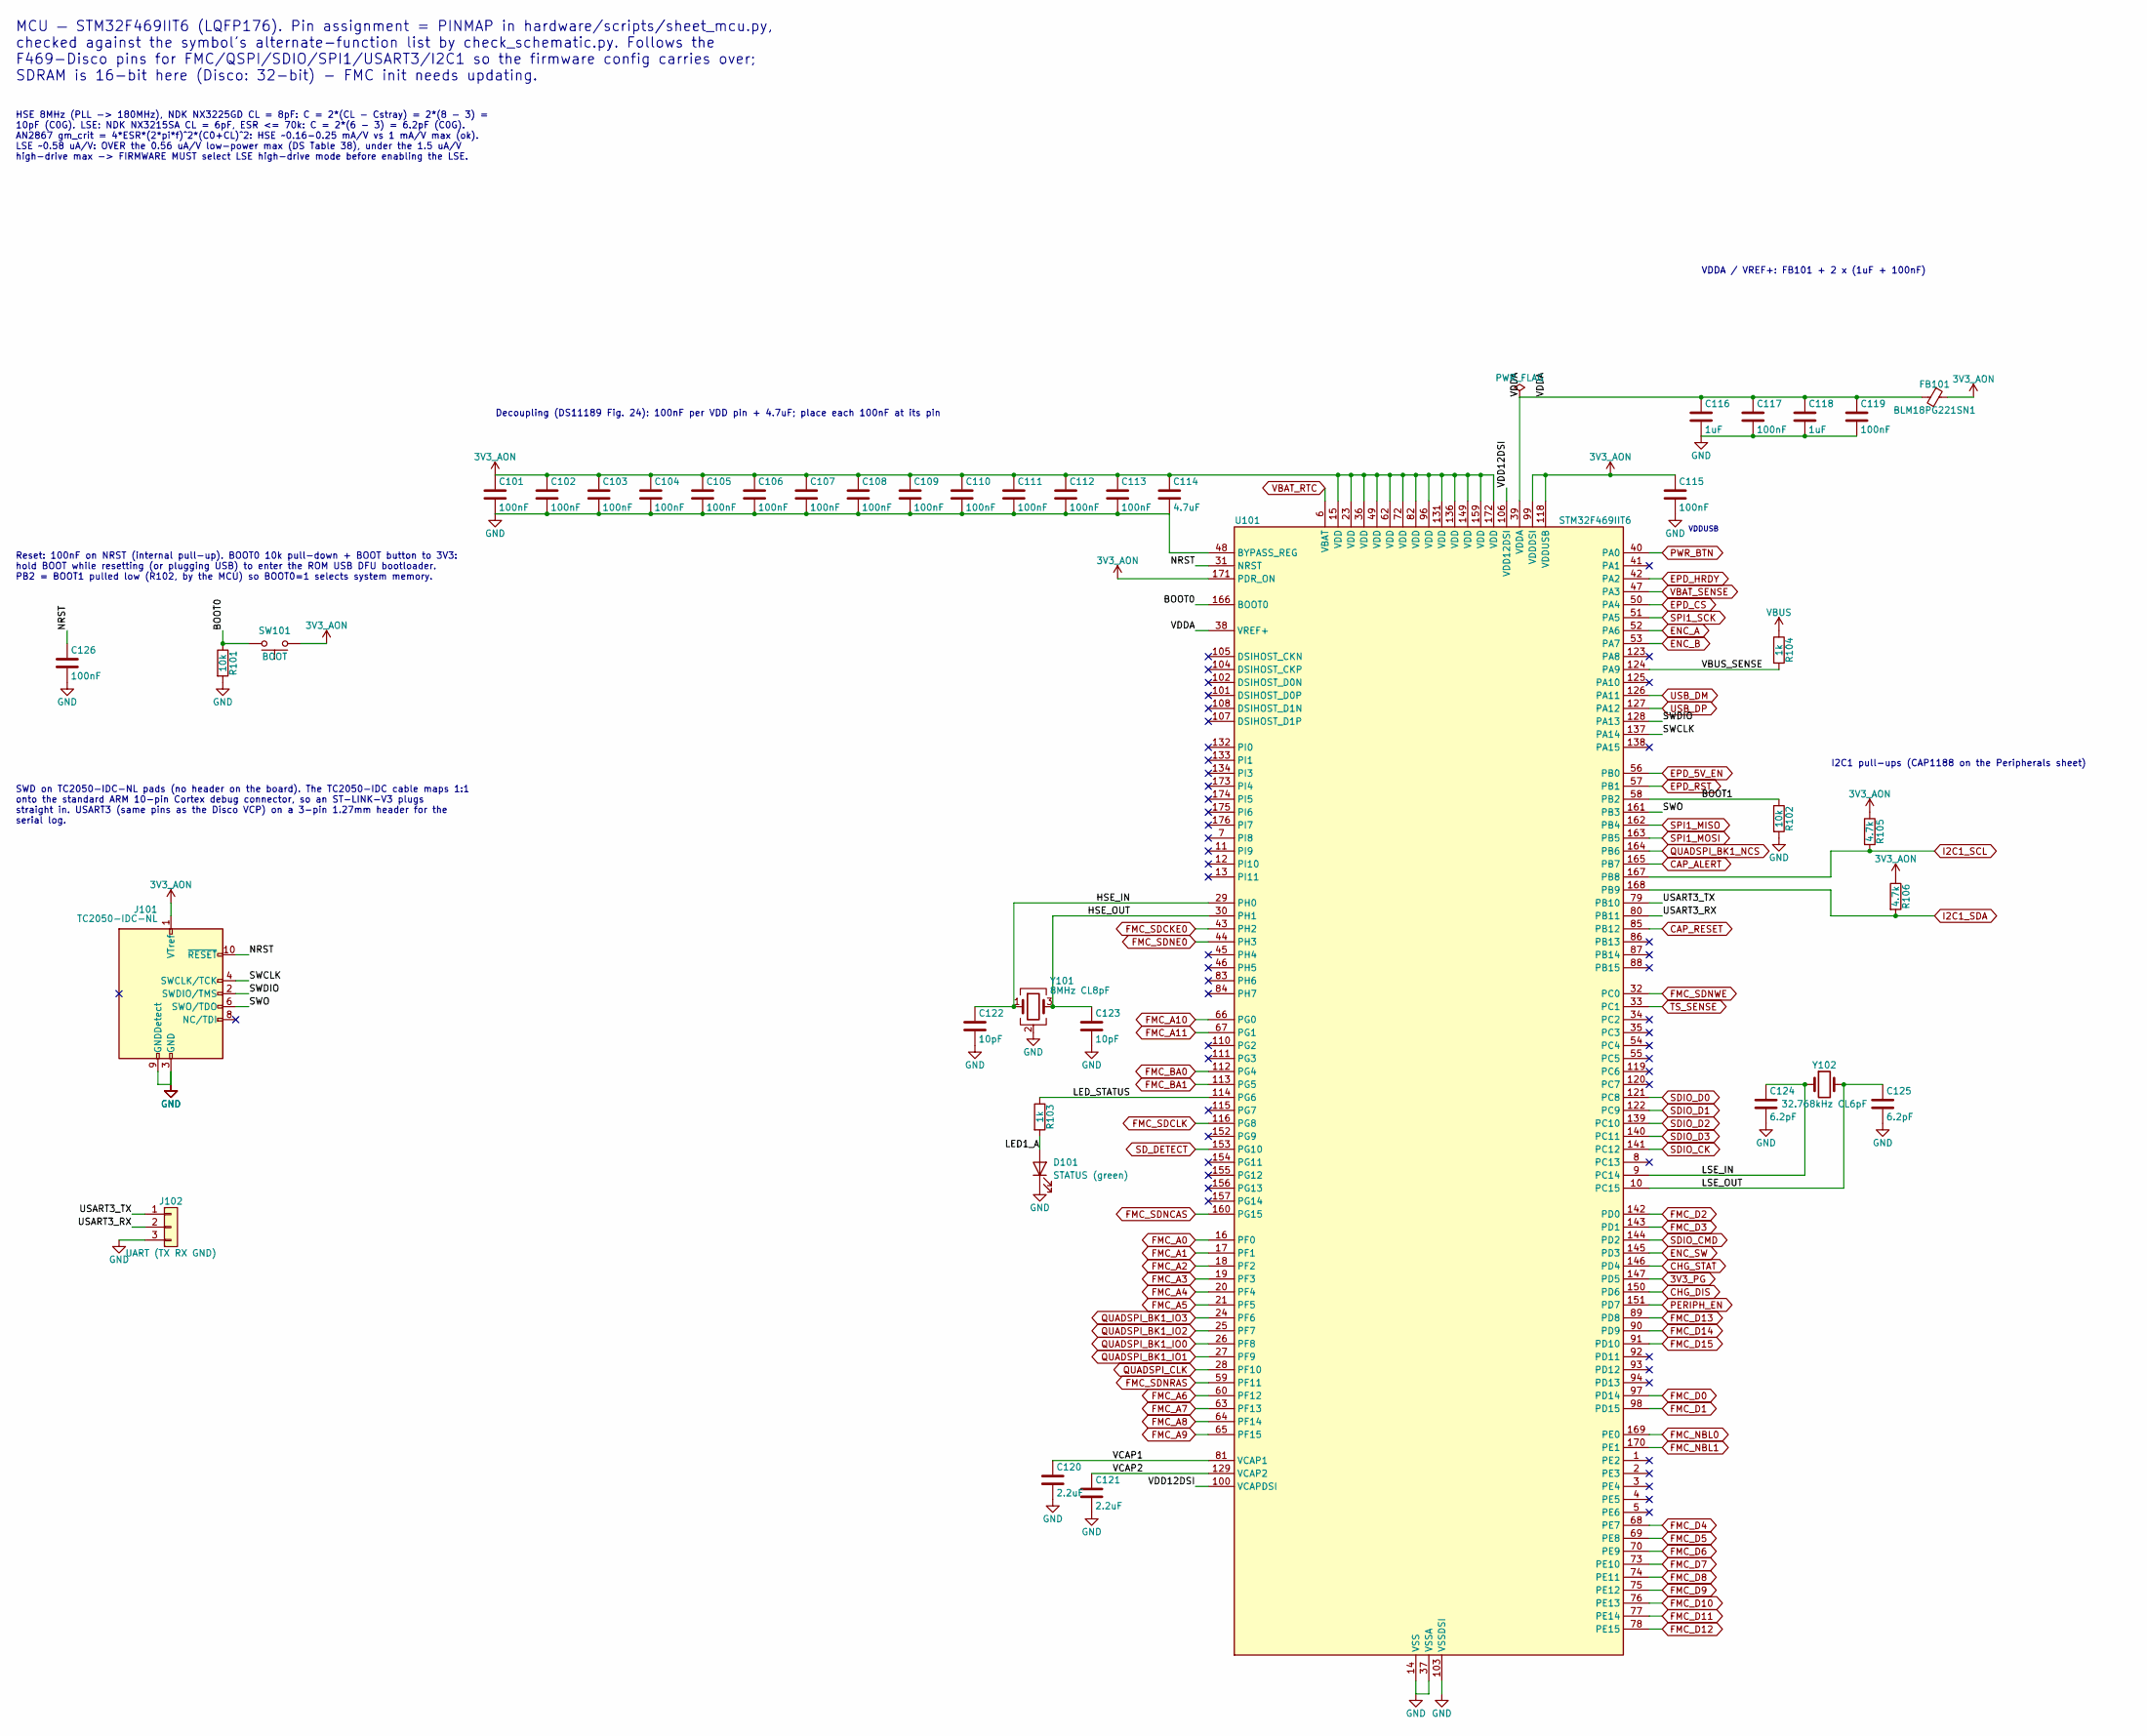
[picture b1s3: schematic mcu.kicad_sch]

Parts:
C101, C102, C103, C104, C105, C106, C107, C108, C109, C110, C111, C112, C113, C115, C117, C119, C126: 100nF; C_0402_1005Metric
C114: 4.7uF; C_0603_1608Metric
C116, C118: 1uF; C_0402_1005Metric
C120, C121: 2.2uF; C_0402_1005Metric
C122, C123: 10pF; C_0402_1005Metric
C124, C125: 6.2pF; C_0402_1005Metric
D101: STATUS (green); LED_0603_1608Metric
FB101: BLM18PG221SN1; L_0603_1608Metric
J101: TC2050-IDC-NL; Tag-Connect_TC2050-IDC-NL_2x05_P1.27mm_Vertical
J102: UART (TX RX GND); PinHeader_1x03_P1.27mm_Vertical
R101, R102: 10k; R_0402_1005Metric
R103, R104: 1k; R_0402_1005Metric
R105, R106: 4.7k; R_0402_1005Metric
SW101: BOOT; SW_Push_1P1T_NO_CK_KMR2
U101: STM32F469IIT6; LQFP-176_24x24mm_P0.5mm; MPN STM32F469IIT6
Y101: 8MHz CL8pF; Crystal_SMD_3225-4Pin_3.2x2.5mm; MPN NX3225GD-8MHZ-STD-CRA-3
Y102: 32.768kHz CL6pF; Crystal_SMD_3215-2Pin_3.2x1.5mm; MPN NX3215SA-32.768KHZ-EXS00A-MU00525

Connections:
3V3_AON: C101.1, C102.1, C103.1, C104.1, C105.1, C106.1, C107.1, C108.1, C109.1, C110.1, C111.1, C112.1, C113.1, C114.1, C115.1, FB101.1, J101.1 (VTref), R105.1, R106.1, SW101.1, U101.15 (VDD), U101.23 (VDD), U101.36 (VDD), U101.49 (VDD), U101.62 (VDD), U101.72 (VDD), U101.82 (VDD), U101.96 (VDD), U101.99 (VDDDSI), U101.118 (VDDUSB), U101.131 (VDD), U101.136 (VDD), U101.149 (VDD), U101.159 (VDD), U101.171 (PDR_ON), U101.172 (VDD); also elsewhere on the board
3V3_PG: U101.147 (PD5); also elsewhere on the board
/MCU/BOOT0: R101.1, SW101.2, U101.166 (BOOT0)
/MCU/BOOT1: R102.1, U101.58 (PB2)
/MCU/HSE_IN: C122.1, U101.29 (PH0), Y101.1
/MCU/HSE_OUT: C123.1, U101.30 (PH1), Y101.3
/MCU/LED1_A: D101.2 (A), R103.2
/MCU/LED_STATUS: R103.1, U101.114 (PG6)
/MCU/LSE_IN: C124.1, U101.9 (PC14), Y102.1
/MCU/LSE_OUT: C125.1, U101.10 (PC15), Y102.2
/MCU/NRST: C126.1, J101.10 (~RESET), U101.31 (NRST)
/MCU/SWCLK: J101.4 (SWCLK/TCK), U101.137 (PA14)
/MCU/SWDIO: J101.2 (SWDIO/TMS), U101.128 (PA13)
/MCU/SWO: J101.6 (SWO/TDO), U101.161 (PB3)
/MCU/USART3_RX: J102.2, U101.80 (PB11)
/MCU/USART3_TX: J102.1, U101.79 (PB10)
/MCU/VBUS_SENSE: R104.2, U101.124 (PA9)
/MCU/VCAP1: C120.1, U101.81 (VCAP1)
/MCU/VCAP2: C121.1, U101.129 (VCAP2)
/MCU/VDD12DSI: U101.100 (VCAPDSI), U101.106 (VDD12DSI)
/MCU/VDDA: C116.1, C117.1, C118.1, C119.1, FB101.2, U101.38 (VREF+), U101.39 (VDDA)
CAP_ALERT: U101.165 (PB7); also elsewhere on the board
CAP_RESET: U101.85 (PB12); also elsewhere on the board
CHG_DIS: U101.150 (PD6); also elsewhere on the board
CHG_STAT: U101.146 (PD4); also elsewhere on the board
ENC_A: U101.52 (PA6); also elsewhere on the board
ENC_B: U101.53 (PA7); also elsewhere on the board
ENC_SW: U101.145 (PD3); also elsewhere on the board
EPD_5V_EN: U101.56 (PB0); also elsewhere on the board
EPD_CS: U101.50 (PA4); also elsewhere on the board
EPD_HRDY: U101.42 (PA2); also elsewhere on the board
EPD_RST: U101.57 (PB1); also elsewhere on the board
FMC_A0: U101.16 (PF0); also elsewhere on the board
FMC_A1: U101.17 (PF1); also elsewhere on the board
FMC_A2: U101.18 (PF2); also elsewhere on the board
FMC_A3: U101.19 (PF3); also elsewhere on the board
FMC_A4: U101.20 (PF4); also elsewhere on the board
FMC_A5: U101.21 (PF5); also elsewhere on the board
FMC_A6: U101.60 (PF12); also elsewhere on the board
FMC_A7: U101.63 (PF13); also elsewhere on the board
FMC_A8: U101.64 (PF14); also elsewhere on the board
FMC_A9: U101.65 (PF15); also elsewhere on the board
FMC_A10: U101.66 (PG0); also elsewhere on the board
FMC_A11: U101.67 (PG1); also elsewhere on the board
FMC_BA0: U101.112 (PG4); also elsewhere on the board
FMC_BA1: U101.113 (PG5); also elsewhere on the board
FMC_D0: U101.97 (PD14); also elsewhere on the board
FMC_D1: U101.98 (PD15); also elsewhere on the board
FMC_D2: U101.142 (PD0); also elsewhere on the board
FMC_D3: U101.143 (PD1); also elsewhere on the board
FMC_D4: U101.68 (PE7); also elsewhere on the board
FMC_D5: U101.69 (PE8); also elsewhere on the board
FMC_D6: U101.70 (PE9); also elsewhere on the board
FMC_D7: U101.73 (PE10); also elsewhere on the board
FMC_D8: U101.74 (PE11); also elsewhere on the board
FMC_D9: U101.75 (PE12); also elsewhere on the board
FMC_D10: U101.76 (PE13); also elsewhere on the board
FMC_D11: U101.77 (PE14); also elsewhere on the board
FMC_D12: U101.78 (PE15); also elsewhere on the board
FMC_D13: U101.89 (PD8); also elsewhere on the board
FMC_D14: U101.90 (PD9); also elsewhere on the board
FMC_D15: U101.91 (PD10); also elsewhere on the board
FMC_NBL0: U101.169 (PE0); also elsewhere on the board
FMC_NBL1: U101.170 (PE1); also elsewhere on the board
FMC_SDCKE0: U101.43 (PH2); also elsewhere on the board
FMC_SDCLK: U101.116 (PG8); also elsewhere on the board
FMC_SDNCAS: U101.160 (PG15); also elsewhere on the board
FMC_SDNE0: U101.44 (PH3); also elsewhere on the board
FMC_SDNRAS: U101.59 (PF11); also elsewhere on the board
FMC_SDNWE: U101.32 (PC0); also elsewhere on the board
GND: C101.2, C102.2, C103.2, C104.2, C105.2, C106.2, C107.2, C108.2, C109.2, C110.2, C111.2, C112.2, C113.2, C114.2, C115.2, C116.2, C117.2, C118.2, C119.2, C120.2, C121.2, C122.2, C123.2, C124.2, C125.2, C126.2, D101.1 (K), J101.3 (GND), J101.5 (GND), J101.9 (GNDDetect), J102.3, R101.2, R102.2, U101.14 (VSS), U101.22 (VSS), U101.37 (VSSA), U101.48 (BYPASS_REG), U101.61 (VSS), U101.71 (VSS), U101.95 (VSS), U101.103 (VSSDSI), U101.109 (VSSDSI), U101.117 (VSS), U101.130 (VSS), U101.135 (VSS), U101.148 (VSS), U101.158 (VSS), Y101.2 (G), Y101.4 (G); also elsewhere on the board
I2C1_SCL: R105.2, U101.167 (PB8); also elsewhere on the board
I2C1_SDA: R106.2, U101.168 (PB9); also elsewhere on the board
PERIPH_EN: U101.151 (PD7); also elsewhere on the board
PWR_BTN: U101.40 (PA0); also elsewhere on the board
QUADSPI_BK1_IO0: U101.26 (PF8); also elsewhere on the board
QUADSPI_BK1_IO1: U101.27 (PF9); also elsewhere on the board
QUADSPI_BK1_IO2: U101.25 (PF7); also elsewhere on the board
QUADSPI_BK1_IO3: U101.24 (PF6); also elsewhere on the board
QUADSPI_BK1_NCS: U101.164 (PB6); also elsewhere on the board
QUADSPI_CLK: U101.28 (PF10); also elsewhere on the board
SDIO_CK: U101.141 (PC12); also elsewhere on the board
SDIO_CMD: U101.144 (PD2); also elsewhere on the board
SDIO_D0: U101.121 (PC8); also elsewhere on the board
SDIO_D1: U101.122 (PC9); also elsewhere on the board
SDIO_D2: U101.139 (PC10); also elsewhere on the board
SDIO_D3: U101.140 (PC11); also elsewhere on the board
SD_DETECT: U101.153 (PG10); also elsewhere on the board
SPI1_MISO: U101.162 (PB4); also elsewhere on the board
SPI1_MOSI: U101.163 (PB5); also elsewhere on the board
SPI1_SCK: U101.51 (PA5); also elsewhere on the board
TS_SENSE: U101.33 (PC1); also elsewhere on the board
USB_DM: U101.126 (PA11); also elsewhere on the board
USB_DP: U101.127 (PA12); also elsewhere on the board
VBAT_RTC: U101.6 (VBAT); also elsewhere on the board
VBAT_SENSE: U101.47 (PA3); also elsewhere on the board
VBUS: R104.1; also elsewhere on the board

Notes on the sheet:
MCU — STM32F469IIT6 (LQFP176). Pin assignment = PINMAP in hardware/scripts/sheet_mcu.py, checked against the symbol's alternate-function list by check_schematic.py. Follows the F469-Disco pins for FMC/QSPI/SDIO/SPI1/USART3/I2C1 so the firmware config carries over; SDRAM is 16-bit here (Disco: 32-bi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
Decoupling (DS11189 Fig. 24): 100nF per VDD pin + 4.7uF; place each 100nF at its pin
VDDUSB
VDDA / VREF+: FB101 + 2 x (1uF + 100nF)
HSE 8MHz (PLL -> 180MHz), NDK NX3225GD CL = 8pF: C = 2*(CL - Cstray) = 2*(8 - 3) = 10pF (C0G). LSE: NDK NX3215SA CL = 6pF, ESR <= 70k: C = 2*(6 - 3) = 6.2pF (C0G). AN2867 gm_crit = 4*ESR*(2*pi*f)^2*(C0+CL)^2: HSE ~0.16-0.25 mA/V vs 1 mA/V max (ok). LSE ~0.58 uA/V: OVER the 0.56 uA/V low-power max (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
I2C1 pull-ups (CAP1188 on the Peripherals sheet)
Reset: 100nF on NRST (internal pull-up). BOOT0 10k pull-down + BOOT button to 3V3: hold BOOT while resetting (or plugging USB) to enter the ROM USB DFU bootloader. PB2 = BOOT1 pulled low (R102, by the MCU) so BOOT0=1 selects system memory.
SWD on TC2050-IDC-NL pads (no header on the board). The TC2050-IDC cable maps 1:1 onto the standard ARM 10-pin Cortex debug connector, so an ST-LINK-V3 plugs straight in. USART3 (same pins as the Disco VCP) on a 3-pin 1.27mm header for the serial log.

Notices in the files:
README.md:
None yet — all rights reserved until a license is chosen.
